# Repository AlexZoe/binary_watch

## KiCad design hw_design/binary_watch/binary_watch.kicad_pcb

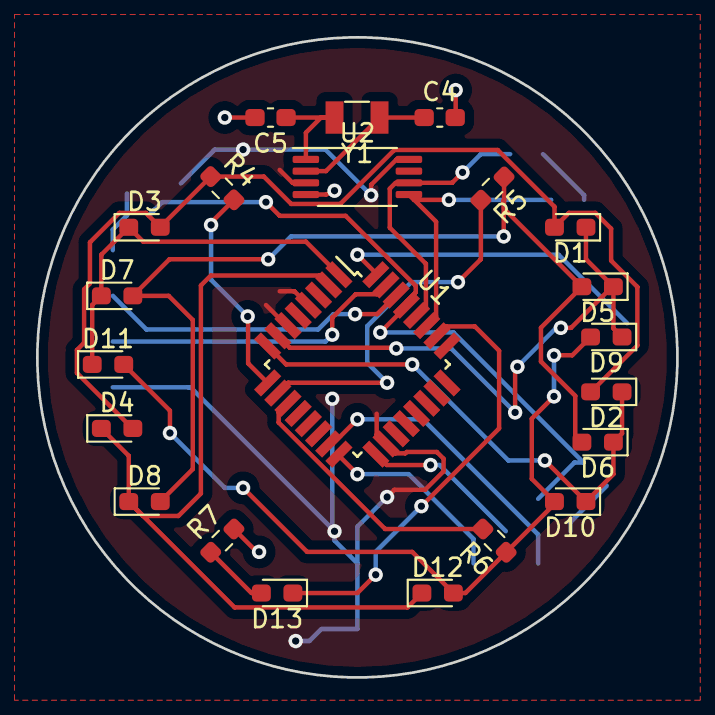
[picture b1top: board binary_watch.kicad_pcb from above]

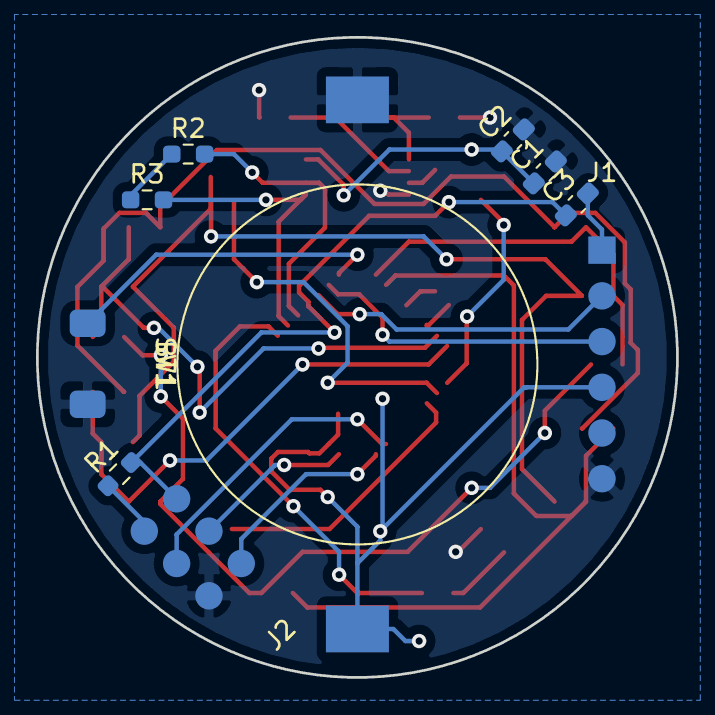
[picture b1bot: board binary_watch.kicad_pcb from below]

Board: 2 copper layers, 35.6 x 35.6 mm, 32 parts (10 on the bottom side), 27 nets.

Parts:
BT1: 3.3V; batt_3V3
C1, C3: 0.1uF; C_0603_1608Metric_Pad1.08x0.95mm_HandSolder
C2: 6.7uF; C_0603_1608Metric_Pad1.08x0.95mm_HandSolder
C4, C5: 7nF; C_0603_1608Metric_Pad1.08x0.95mm_HandSolder
D1, D2, D3, D4, D5, D6, D7, D8, D9, D10, D11, D12, D13: LED; LED_0603_1608Metric_Pad1.05x0.95mm_HandSolder
J1: Conn_01x06; Conn1x6
J2: Conn_02x03_Counter_Clockwise; Conn2x3
R1, R2, R3: 10k; R_0603_1608Metric_Pad0.98x0.95mm_HandSolder
R4, R5, R6, R7: 330; R_0603_1608Metric_Pad0.98x0.95mm_HandSolder
SW1: SW_Push; push_4.5mm
U1: ATmega328P-AU; TQFP-32_7x7mm_P0.8mm
U2: MCP7940N-xMS; TSSOP-8_4.4x3mm_P0.65mm
Y1: 32.758kHz; Crystal_SMD_3215-2Pin_3.2x1.5mm

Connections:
/MISO: J2.1, U1.16
/MOSI: J2.5, U1.15
/RST: C3.1, J2.3, R1.2, U1.29
/SCL: R2.2, U1.28, U2.6
/SCLK: J2.2, U1.17
/SDA: R3.2, U1.27, U2.5
GND: BT1.2, C1.2, C2.2, C4.2, C5.2, J1.6, J2.4, R7.2, SW1.2, U2.4
unnamed: C3.2, J1.1
unnamed: C4.1, U2.2, Y1.2
unnamed: C5.1, U2.1, Y1.1
unnamed: D1.1, D5.1, D9.1, U1.7
unnamed: D1.2, D2.2, D3.2, D4.2, R4.1
unnamed: D5.2, D6.2, D7.2, D8.2, R5.1
unnamed: D2.1, D6.1, D10.1, U1.8
unnamed: D9.2, D10.2, D11.2, D12.2, R6.1
unnamed: D3.1, D7.1, D11.1, U1.1
unnamed: D4.1, D8.1, D12.1, U1.2
unnamed: D13.1, U1.26
unnamed: D13.2, R7.1
unnamed: J1.2, U1.30
unnamed: J1.3, U1.31
unnamed: R4.2, U1.9
unnamed: R5.2, U1.10
unnamed: R6.2, U1.11
unnamed: SW1.1, U1.32
unnamed: U1.3, U1.5, U1.21
VCC: BT1.1, C1.1, C2.1, J1.4, J2.6, R1.1, R2.1, R3.1, U1.4, U1.6, U1.18, U2.3, U2.8

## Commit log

2020-11-10 [feat] Add Schematic and Footprints
2020-11-14 [rework] Remove Additional Buttons
    Only keep a single button for user input.
    Use button press timings to cycle between modes and information
    to be displayed.
2020-11-14 [wip] Add PCB Layout
    Add first revision of the PCB layout.
    Does not include any routing.
2020-11-14 [fix] Move Condensator
    Connect Condensator C3 between Reset and DTR.
2020-11-14 [update] Place PCB Components
    Place all components on pcb layout to start routing.
2021-05-05 [update] Schematic and PCB
2021-05-05 [doc] Add License
2021-05-05 [fix] License
